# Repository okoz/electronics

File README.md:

# Random Electronic Things

Things in this repo:

- [flip-flop](flip-flop) - A flip-flop circuit that I used to try etching a board.
- [eeprom-programmer](eeprom-programmer) - Hardware and firmware for an EEPROM programmer.
- [negative-voltage](negative-voltage) - A negative voltage generator.
- [hardcaml-mmu](hardcaml-mmu) - Getting HardCaml to work; an MMU for a 65C02 microcomputer.
- [max232-adapter](max232-adapter) - A MAX232 board for converting between RS232 and 5V CMOS logic levels.

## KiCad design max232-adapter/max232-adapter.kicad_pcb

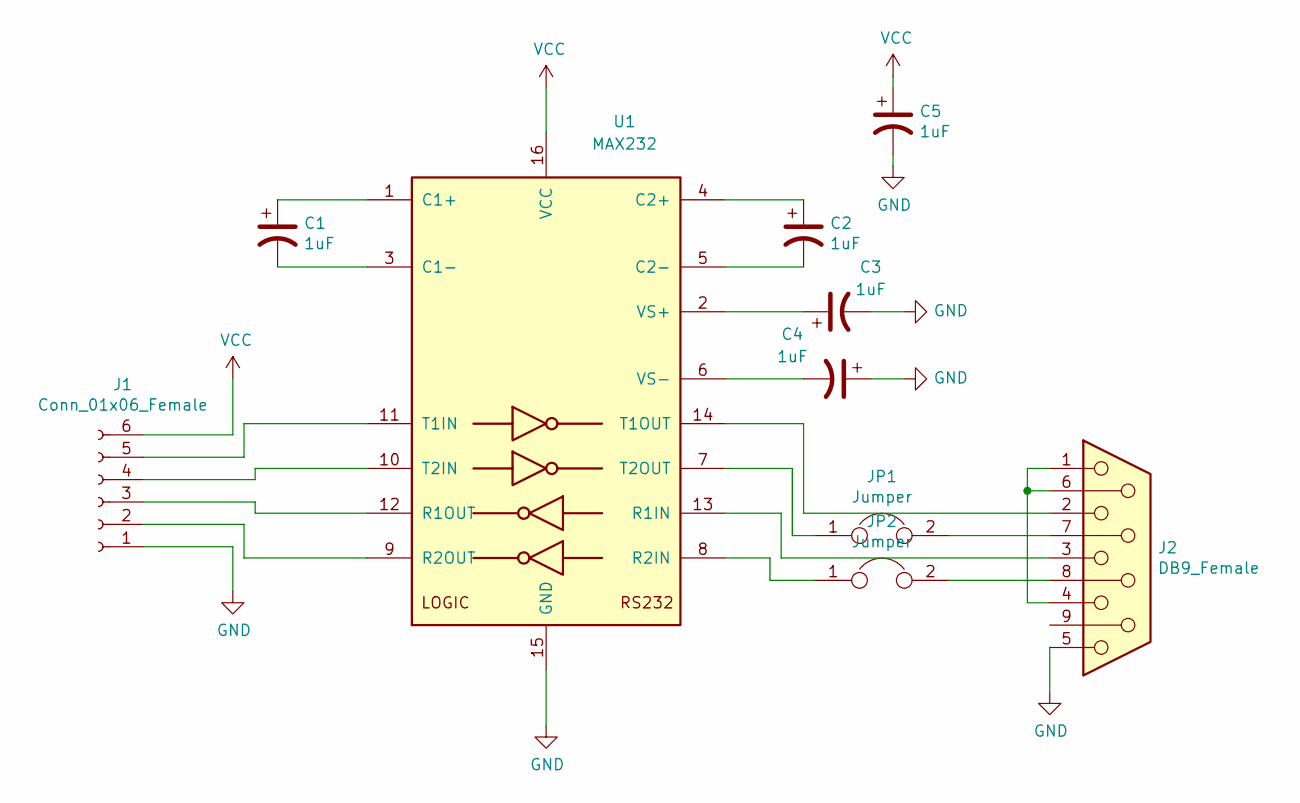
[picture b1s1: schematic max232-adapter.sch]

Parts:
C1, C2, C3, C4, C5: 1uF; CP_Radial_D5.0mm_P2.50mm
J1: Conn_01x06_Female; PinHeader_1x06_P2.54mm_Vertical
J2: DB9_Female; DSUB-9_Female_Horizontal_P2.77x2.84mm_EdgePinOffset9.90mm_H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
JP1, JP2: Jumper; PinHeader_1x02_P2.54mm_Vertical
U1: MAX232; DIP-16_W7.62mm_Socket_LongPads

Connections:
GND: C3.2, C4.1, C5.2, J1.1, J2.5, U1.15 (GND)
unnamed: C1.1, U1.1 (C1+)
unnamed: C1.2, U1.3 (C1-)
unnamed: C2.1, U1.4 (C2+)
unnamed: C2.2, U1.5 (C2-)
unnamed: C3.1, U1.2 (VS+)
unnamed: C4.2, U1.6 (VS-)
unnamed: J1.2, U1.9 (R2OUT)
unnamed: J1.3, U1.12 (R1OUT)
unnamed: J1.4, U1.10 (T2IN)
unnamed: J1.5, U1.11 (T1IN)
unnamed: J2.1, J2.4, J2.6
unnamed: J2.2, U1.14 (T1OUT)
unnamed: J2.3, U1.13 (R1IN)
unnamed: J2.7, JP1.2
unnamed: J2.8, JP2.2
unnamed: JP1.1, U1.7 (T2OUT)
unnamed: JP2.1, U1.8 (R2IN)
VCC: C5.1, J1.6, U1.16 (VCC)

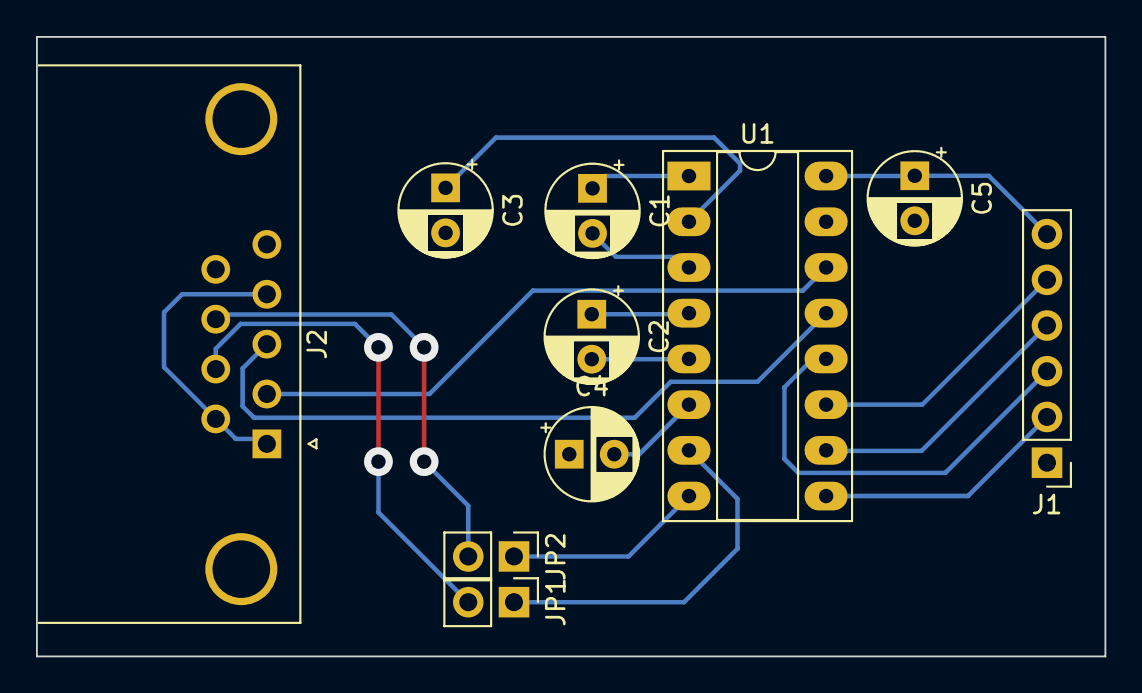
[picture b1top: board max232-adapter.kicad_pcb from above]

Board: 2 copper layers, 59.4 x 34.4 mm, 10 parts (0 on the bottom side), 19 nets.

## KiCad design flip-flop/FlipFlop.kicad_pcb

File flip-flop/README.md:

# Flip-Flop

Storage for 1-bit of information but only when it's sunny:

Here are some photos half way through assembly along with a screenshot from
KiCad. Behold the red solder mask! This is the first board I've ever etched.

Front                     | PCB                 | Back
:------------------------:|:-------------------:|:------------------------:
 |  |

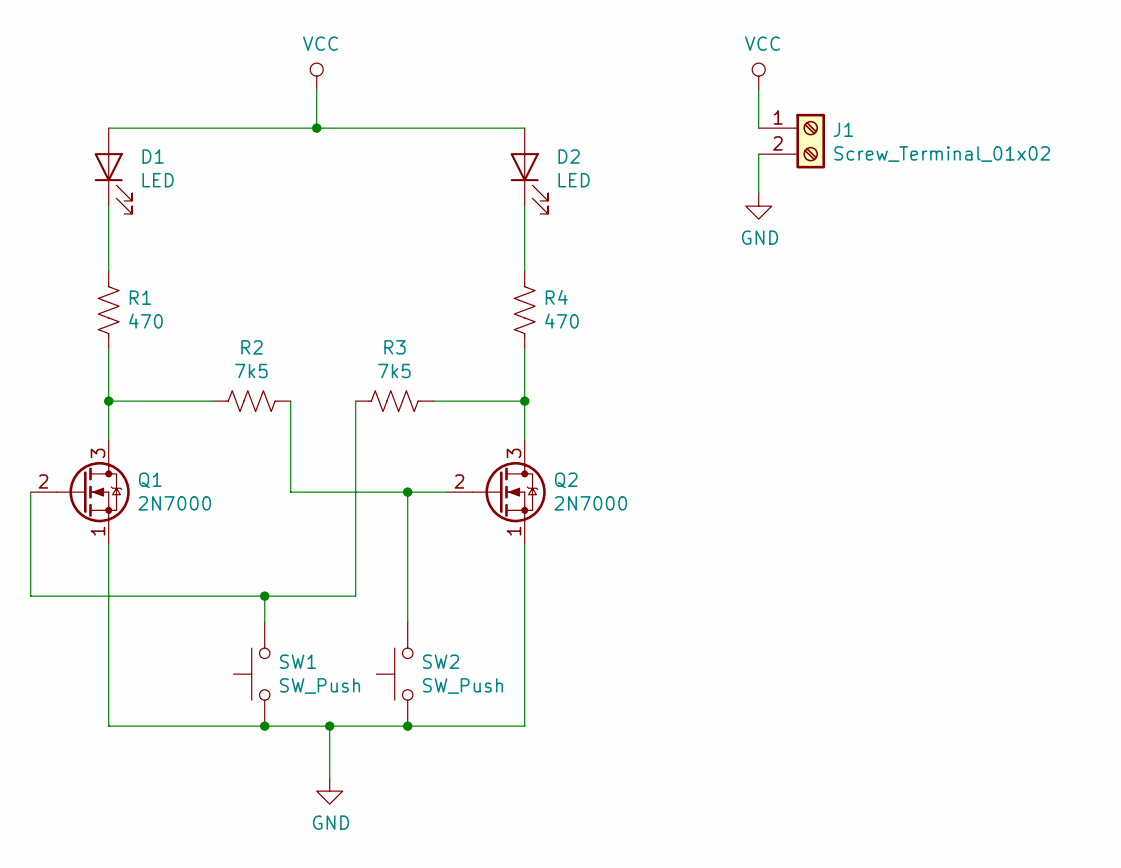
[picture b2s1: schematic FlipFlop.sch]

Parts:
D1, D2: LED; LED_D5.0mm
J1: Screw_Terminal_01x02; TerminalBlock_bornier-2_P5.08mm
Q1, Q2: 2N7000; TO-92_Inline
R1, R4: 470; R_Axial_DIN0207_L6.3mm_D2.5mm_P10.16mm_Horizontal
R2, R3: 7k5; R_Axial_DIN0207_L6.3mm_D2.5mm_P10.16mm_Horizontal
SW1, SW2: SW_Push; SW_PUSH-12mm

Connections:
GND: J1.2, Q1.1 (S), Q2.1 (S), SW1.1, SW2.1
unnamed: D1.1 (K), R1.1
unnamed: D2.1 (K), R4.1
unnamed: Q1.2 (G), R3.2, SW1.2
unnamed: Q1.3 (D), R1.2, R2.2
unnamed: Q2.2 (G), R2.1, SW2.2
unnamed: Q2.3 (D), R3.1, R4.2
VCC: D1.2 (A), D2.2 (A), J1.1

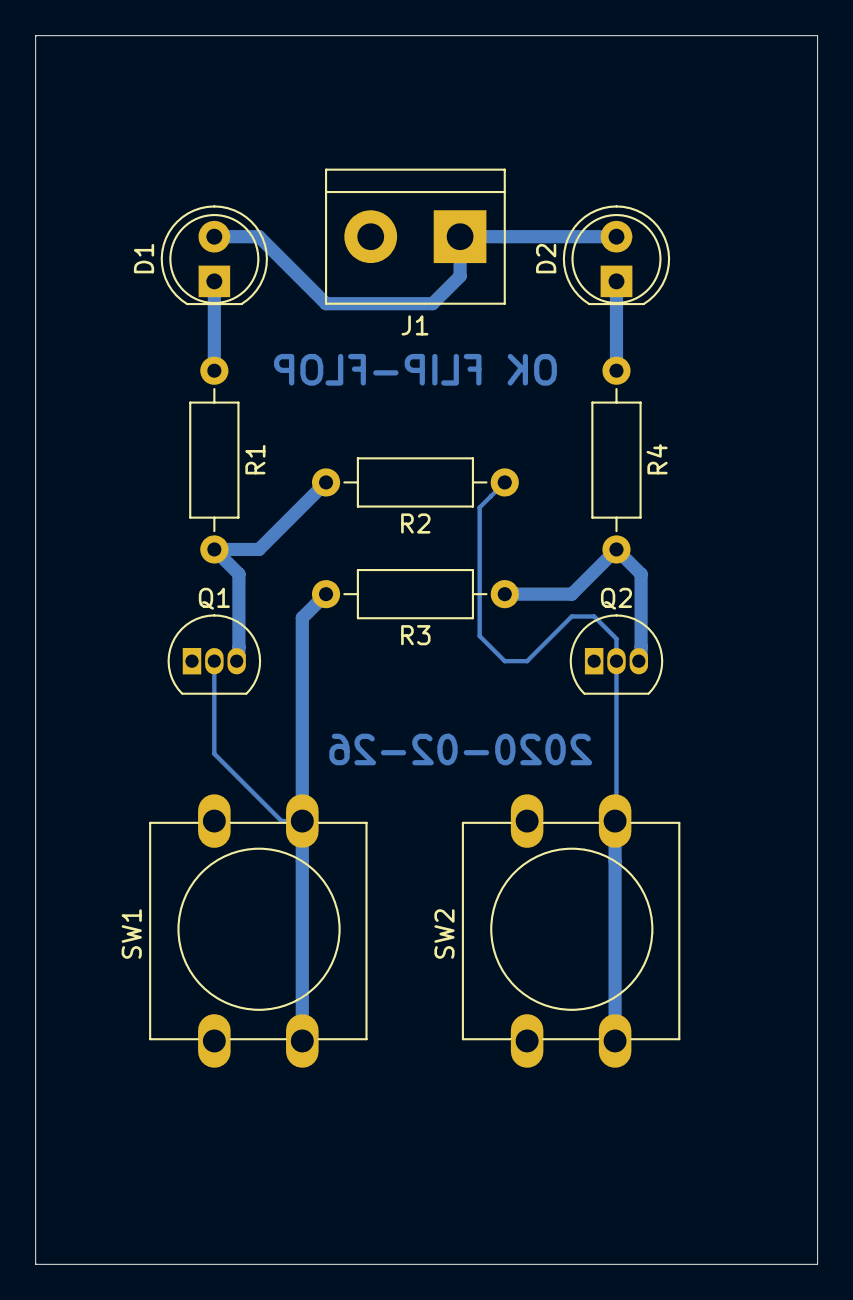
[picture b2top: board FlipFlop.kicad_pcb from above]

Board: 2 copper layers, 44.4 x 69.8 mm, 11 parts (0 on the bottom side), 8 nets.

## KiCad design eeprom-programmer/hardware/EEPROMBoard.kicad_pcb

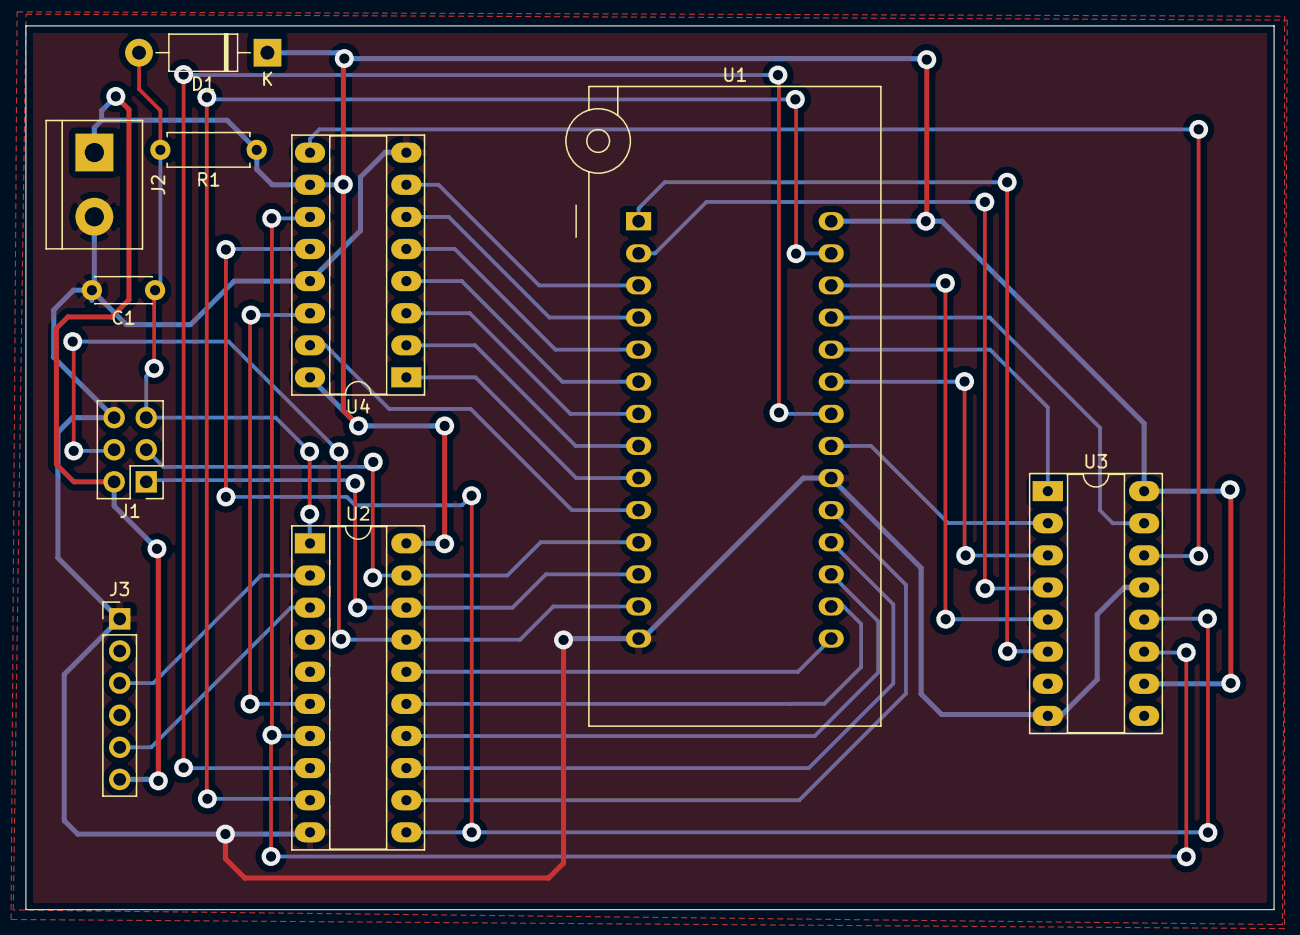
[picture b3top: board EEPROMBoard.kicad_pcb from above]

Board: 2 copper layers, 98.8 x 69.9 mm, 10 parts (0 on the bottom side), 34 nets.

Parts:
C1: 10u; C_Disc_D4.3mm_W1.9mm_P5.00mm
D1: 1N4001; D_DO-41_SOD81_P10.16mm_Horizontal
J1: Conn_02x03_Odd_Even; PinHeader_2x03_P2.54mm_Vertical
J2: Screw_Terminal_01x02; TerminalBlock_bornier-2_P5.08mm
J3: Conn_01x06; PinHeader_1x06_P2.54mm_Vertical
R1: 10k; R_Axial_DIN0207_L6.3mm_D2.5mm_P7.62mm_Horizontal
U1: 28C256; DIP_Socket-28_W11.9_W12.7_W15.24_W17.78_W18.5_3M_228-1277-0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
U2: ATtiny2313V-10PU; DIP-20_W7.62mm_Socket_LongPads
U3, U4: 74HC595; DIP-16_W7.62mm_Socket_LongPads

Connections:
ADDRESS_BUS0: U1.10, U4.15
ADDRESS_BUS1: U1.9, U4.1
ADDRESS_BUS2: U1.8, U4.2
ADDRESS_BUS3: U1.7, U4.3
ADDRESS_BUS4: U1.6, U4.4
ADDRESS_BUS5: U1.5, U4.5
ADDRESS_BUS6: U1.4, U4.6
ADDRESS_BUS7: U1.3, U4.7
ADDRESS_BUS8: U1.25, U3.15
ADDRESS_BUS9: U1.24, U3.1
ADDRESS_BUS10: U1.21, U3.2
ADDRESS_BUS11: U1.23, U3.3
ADDRESS_BUS12: U1.2, U3.4
ADDRESS_BUS13: U1.26, U3.5
ADDRESS_BUS14: U1.1, U3.6
ADDR_OUTPUT: U2.6, U4.14
ADDR_RCLK: U2.11, U3.12, U4.12
ADDR_SRCLK: U2.7, U3.11, U4.11
DATA_BUS0: J1.3, U1.11, U2.19
DATA_BUS1: J1.1, U1.12, U2.18
DATA_BUS2: J1.4, U1.13, U2.17
DATA_BUS3: U1.15, U2.16
DATA_BUS4: U1.16, U2.15
DATA_BUS5: U1.17, U2.14
DATA_BUS6: U1.18, U2.13
DATA_BUS7: U1.19, U2.12
GND: C1.2, J1.6, J2.2, J3.1, U1.14, U1.20, U2.10, U3.8, U3.13, U4.8, U4.13
unnamed: J3.3, U2.2
unnamed: J3.5, U2.3
unnamed: U3.14, U4.9
unnamed: C1.1, D1.2, J1.5, R1.2, U2.1
VCC: D1.1, J1.2, J2.1, J3.6, R1.1, U1.28, U2.20, U3.10, U3.16, U4.10, U4.16
~EEPROM_OE: U1.22, U2.8
~EEPROM_WE: U1.27, U2.9

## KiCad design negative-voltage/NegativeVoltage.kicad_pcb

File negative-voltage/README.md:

# Negative Voltage Generator

The schematic is specified in SKiDL and the resulting netlist is imported in
KiCad for board layout.  This is the second board I've ever etched.

Side                  | Image 
:--------------------:|:-------------------:
Front                 | 
PCB                   | 
Back                  |

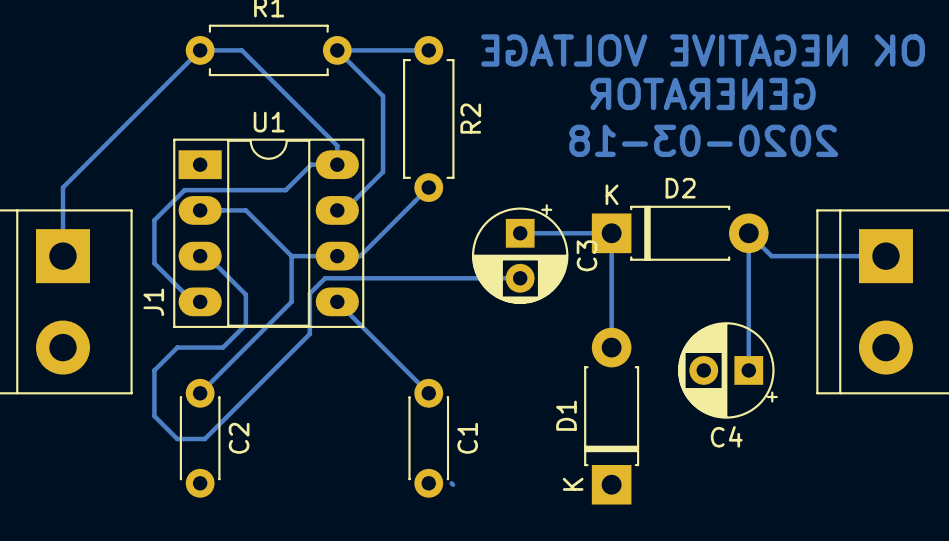
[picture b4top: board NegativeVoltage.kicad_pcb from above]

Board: 2 copper layers, 11 parts (0 on the bottom side), 8 nets.

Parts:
C1: 0.1uF; C_Disc_D4.3mm_W1.9mm_P5.00mm
C2: 0.022uF; C_Disc_D4.3mm_W1.9mm_P5.00mm
C3, C4: 22uF; CP_Radial_D5.0mm_P2.50mm
D1, D2: 1N4001; D_DO-41_SOD81_P7.62mm_Horizontal
J1, J2: Screw_Terminal_01x02; TerminalBlock_bornier-2_P5.08mm
R1: 1k; R_Axial_DIN0207_L6.3mm_D2.5mm_P7.62mm_Horizontal
R2: 10k; R_Axial_DIN0207_L6.3mm_D2.5mm_P7.62mm_Horizontal
U1: LM555; DIP-8_W7.62mm_Socket_LongPads

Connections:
GND: C1.2, C2.2, C4.2, D1.1, J1.2, J2.2, U1.1
unnamed: C2.1, R2.2, U1.2, U1.6
unnamed: C1.1, U1.5
unnamed: R1.2, R2.1, U1.7
unnamed: C3.1, D1.2, D2.1
unnamed: C4.1, D2.2, J2.1
PWM_SIGNAL: C3.2, U1.3
VCC: J1.1, R1.1, U1.4, U1.8

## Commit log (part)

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2020-02-28 Add test flip-flop circuit for etching
2020-02-28 Add README.md
2020-03-07 Not sure what changed
2020-03-15 Add EEPROM programmer hardware
2020-03-15 Could this be it?
2020-03-15 Add some headers to make a 28-pin ZIF socket into a 40 pin one.
2020-03-16 Add ISP connector
2020-03-17 Reset PCB
2020-03-18 Add package requirements
2020-03-18 Remove BOM from requirements.txt
2020-03-18 Initial commit of the negative voltage generator
2020-03-18 Add a PCB
2020-03-18 Initial routing
2020-03-19 Separate charge pump circuit
2020-03-19 Add second version with only one sided routing
2020-03-19 Moves some stuff around
2020-03-21 Increase solder mask clearance
2020-03-21 Add negative voltage generator link
2020-03-21 Add board images
2020-03-21 Add images
2020-03-21 Make a subcircuit for the pwm generator
2020-03-24 Add a landing page for the flip-flop
2020-03-24 Images working?
2020-03-24 Smaller images
2020-03-24 Try a table
2020-03-24 Bigger images
2020-03-24 Add pcb image
2020-03-24 Formatting
2020-03-24 Test
2020-03-24 Test table
2020-03-24 The :'s mean center alignment
2020-03-24 Add PCB image for negative voltage generator
2020-03-24 back.jpg
2020-03-24 Consistent image names
2020-03-24 Stick with transposed table
2020-03-24 Test of an MMU for a 65C02 microcomputer
2020-03-24 Add hardcaml-mmu
2020-03-24 Add links
2020-03-24 Maybe fix spaces
2020-03-24 Cleanup
2020-03-24 Fix spaces
2020-03-24 Build details
2020-03-26 Add MMU with bootstrapping
2020-03-26 English
2020-03-28 Spelling
2020-03-28 Make a separate module for the memory copier
2020-03-29 Add mmu module
2020-03-29 Add an MMU test
2020-03-29 Start working on the memory copier test
2020-03-29 Memory copier works
2020-03-29 Spaces
2020-03-29 More spaces
2020-03-29 Add memory copier description
2020-03-29 More words
2020-07-12 Add RS232 adapter
2020-07-12 PCB layout finished... Will it really work?
2020-07-19 Add EEPROM programmer firmware
2020-07-19 Move things into modules
2020-07-19 Reading seems to work, writing doesn't
2020-07-23 Simplify!
2020-07-28 Fixed EEPROM writing. Not converting data written into single bytes was the issue
2025-08-22 Bump future from 0.18.2 to 1.0.0 in /negative-voltage
    Bumps [future](https://github.com/PythonCharmers/python-future) from 0.18.2 to 1.0.0.
    - [Release notes](https://github.com/PythonCharmers/python-future/releases)
    - [Changelog](https://github.com/PythonCharmers/python-future/blob/master/docs/changelog.rst)
    - [Commits](https://github.com/PythonCharmers/python-future/compare/v0.18.2...v1.0.0)
    ---
    updated-dependencies:
